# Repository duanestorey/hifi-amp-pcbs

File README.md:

## Hi-Fidelity Amplifier With Active-Crossovers and Room Correction

These are the PCBs representing a two-year passive effort to create, from scratch, an entire hi-fi amplifier with built-in DSP support for active crossovers and room 
correction.  You can [explore the individual PCBs for this project here](/pcbs).

### Overview

The amplifier has the following specifications:

* Four LM3886 68W amplifier channels in two monoblocks
* Five line-level RCA analog inputs
* One phono/vinyl RCA input with built-in amplifier and RIAA correction
* Four 192kHz/24-bit digital SPDIF inputs and one TOSLINK optical
* Multiple 192kHz/24-bit Burr-brown digital to analog converters
* IR remote connection, and built-in web server for configuration and web-app access
* Custom digital signal processor with active-crossovers and room correction ability based on biquad filters and parametric EQ
* Over-the-air code updates and wifi diagnostic information 

### Project Style Guide

#### Power Monitors

There are several INA260 power meters.  

1) MAIN Digital/Analog PSU monitor, address GND/SCL
2) MAIN Positive rail for channel amplifiers, address SCL/GND
3) 7V to 5V converter, address GND/GND
4) 7V to 3V converter, address GND/3V
5) Positive analog converter,  3V/GND
6) Entire 7V converter, 3V/3V

#### Temperature Sensors

1) Microprocessor board, address GND/GND
2) Digital/Analog PSU, address GND/3V#
3) Monoblocks 1, address 3V3/GND and 3V3/3V3
4) DSP, address float/GND

#### LED lights and resistors

The following voltages and LED colours should be used for consistency. In general, all LEDs are set at 2ma of current are 0603 size.

##### Digital Voltages

- 3.3V - Blue, set to ~2ma using 150R 
- 5.0V - Red, set to ~2ma using 1.3K

##### Analog Voltages

* +3.3V - Yellow, set to ~2ma using 620R
* +9.5V - Yellow, set to ~2ma using 3.6K
* -9.5V - Blue, set to ~2ma using 3.3K
* +34V - Yellow, set to ~2ma using 16K
* -34V - Blue, set to ~2ma using 16K
* 12V - Red, set to ~2ma using 4.7K
* Positive DC - Yellow, set to 2ma
* Negative DC - Blue, set to 2ma

#### SPDIF

- TODO: ADded more inputs
- TODO: Maybe add isolation transformers
- TODO: Change ground plane so SPDIF ground doesn't interfere with analog DAC ground

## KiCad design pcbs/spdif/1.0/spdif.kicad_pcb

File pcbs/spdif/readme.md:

## SPDIF transceiver 

This board provides decoding for up to 5 SPDIF/TOSLINK digital audio connections.  It allows has two I2S inputs (one for the microprocessor, and one from the analog ADC board) which can be routed to the output.

### Version History

- 1.0: Initial Release

### Speciality Compenents

* DIX9211 216-kHz Digital Audio Interface Transceiver

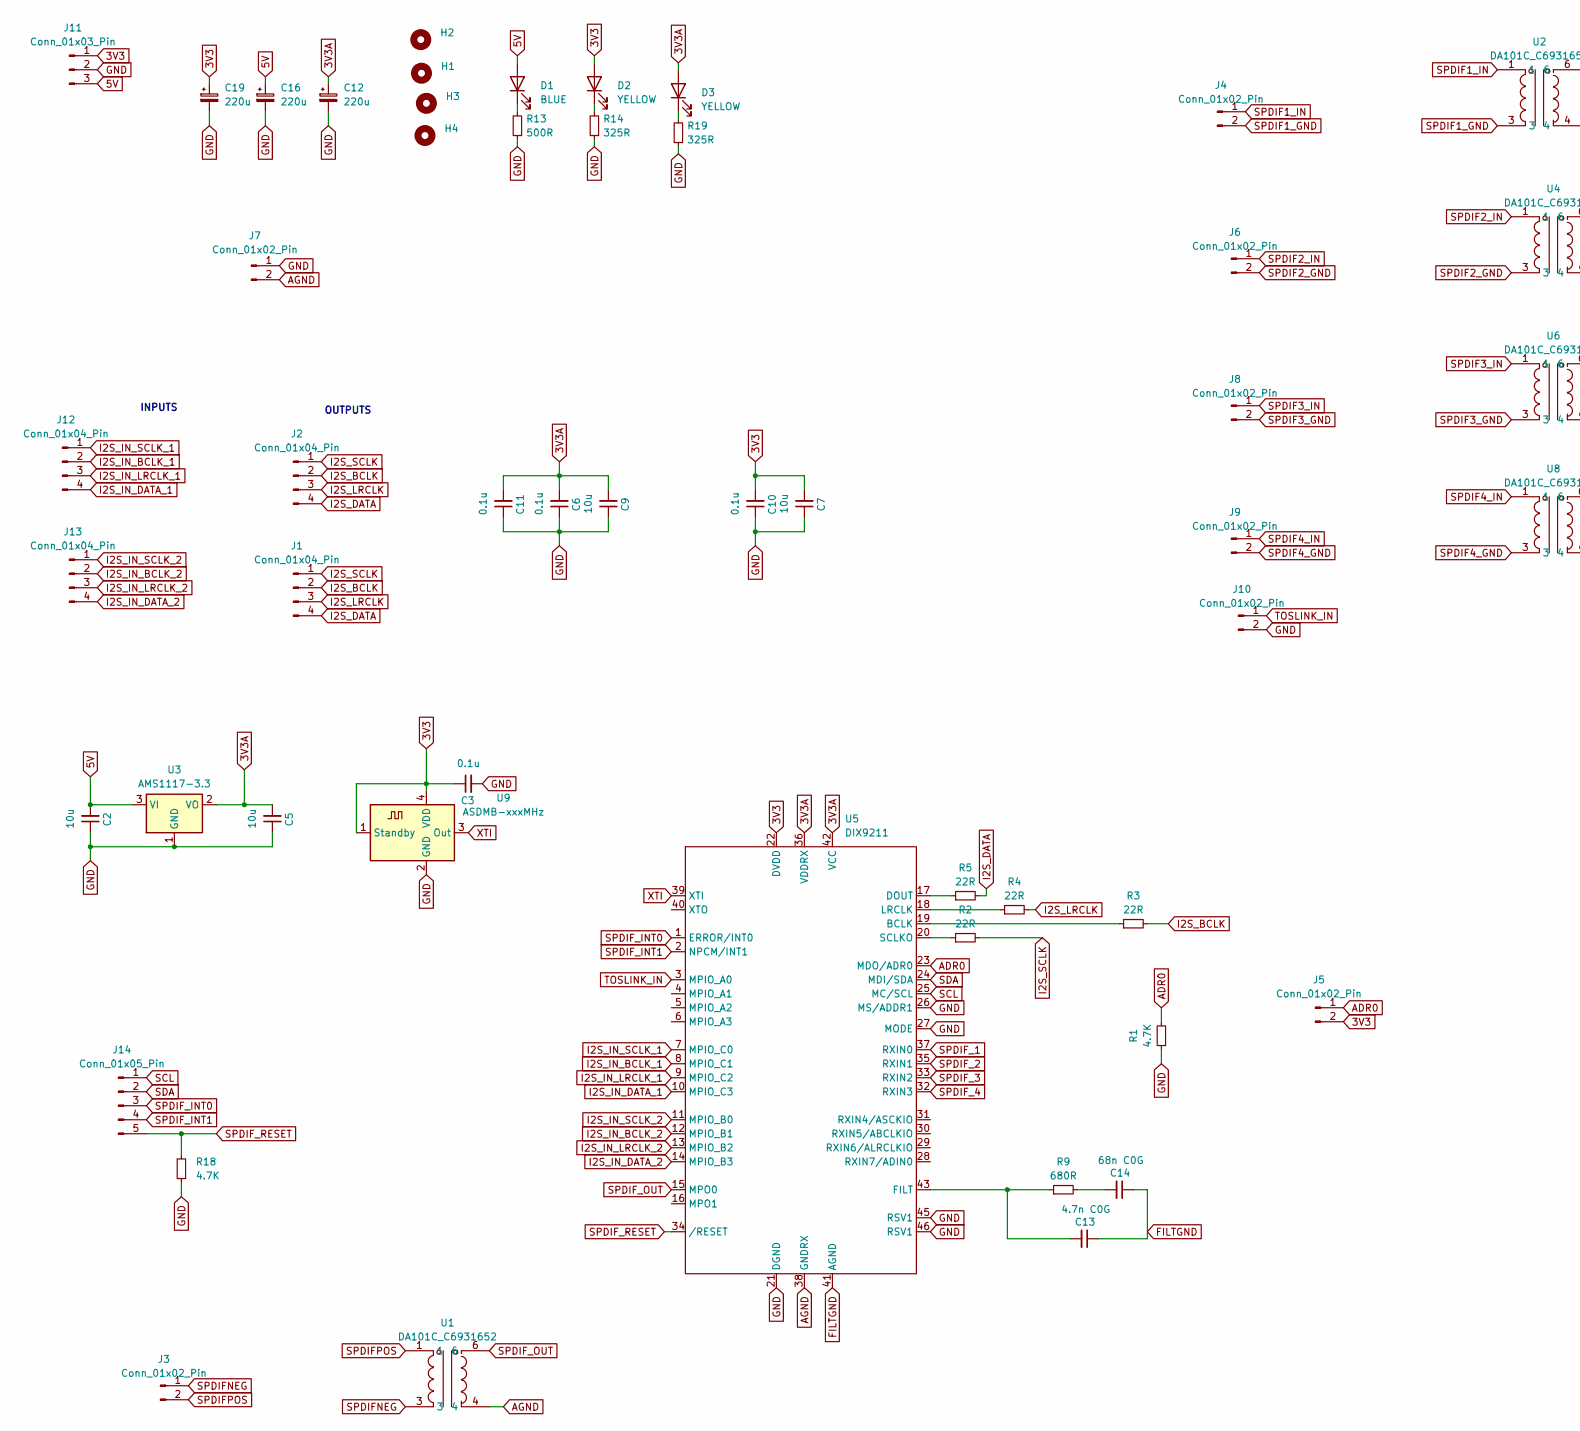
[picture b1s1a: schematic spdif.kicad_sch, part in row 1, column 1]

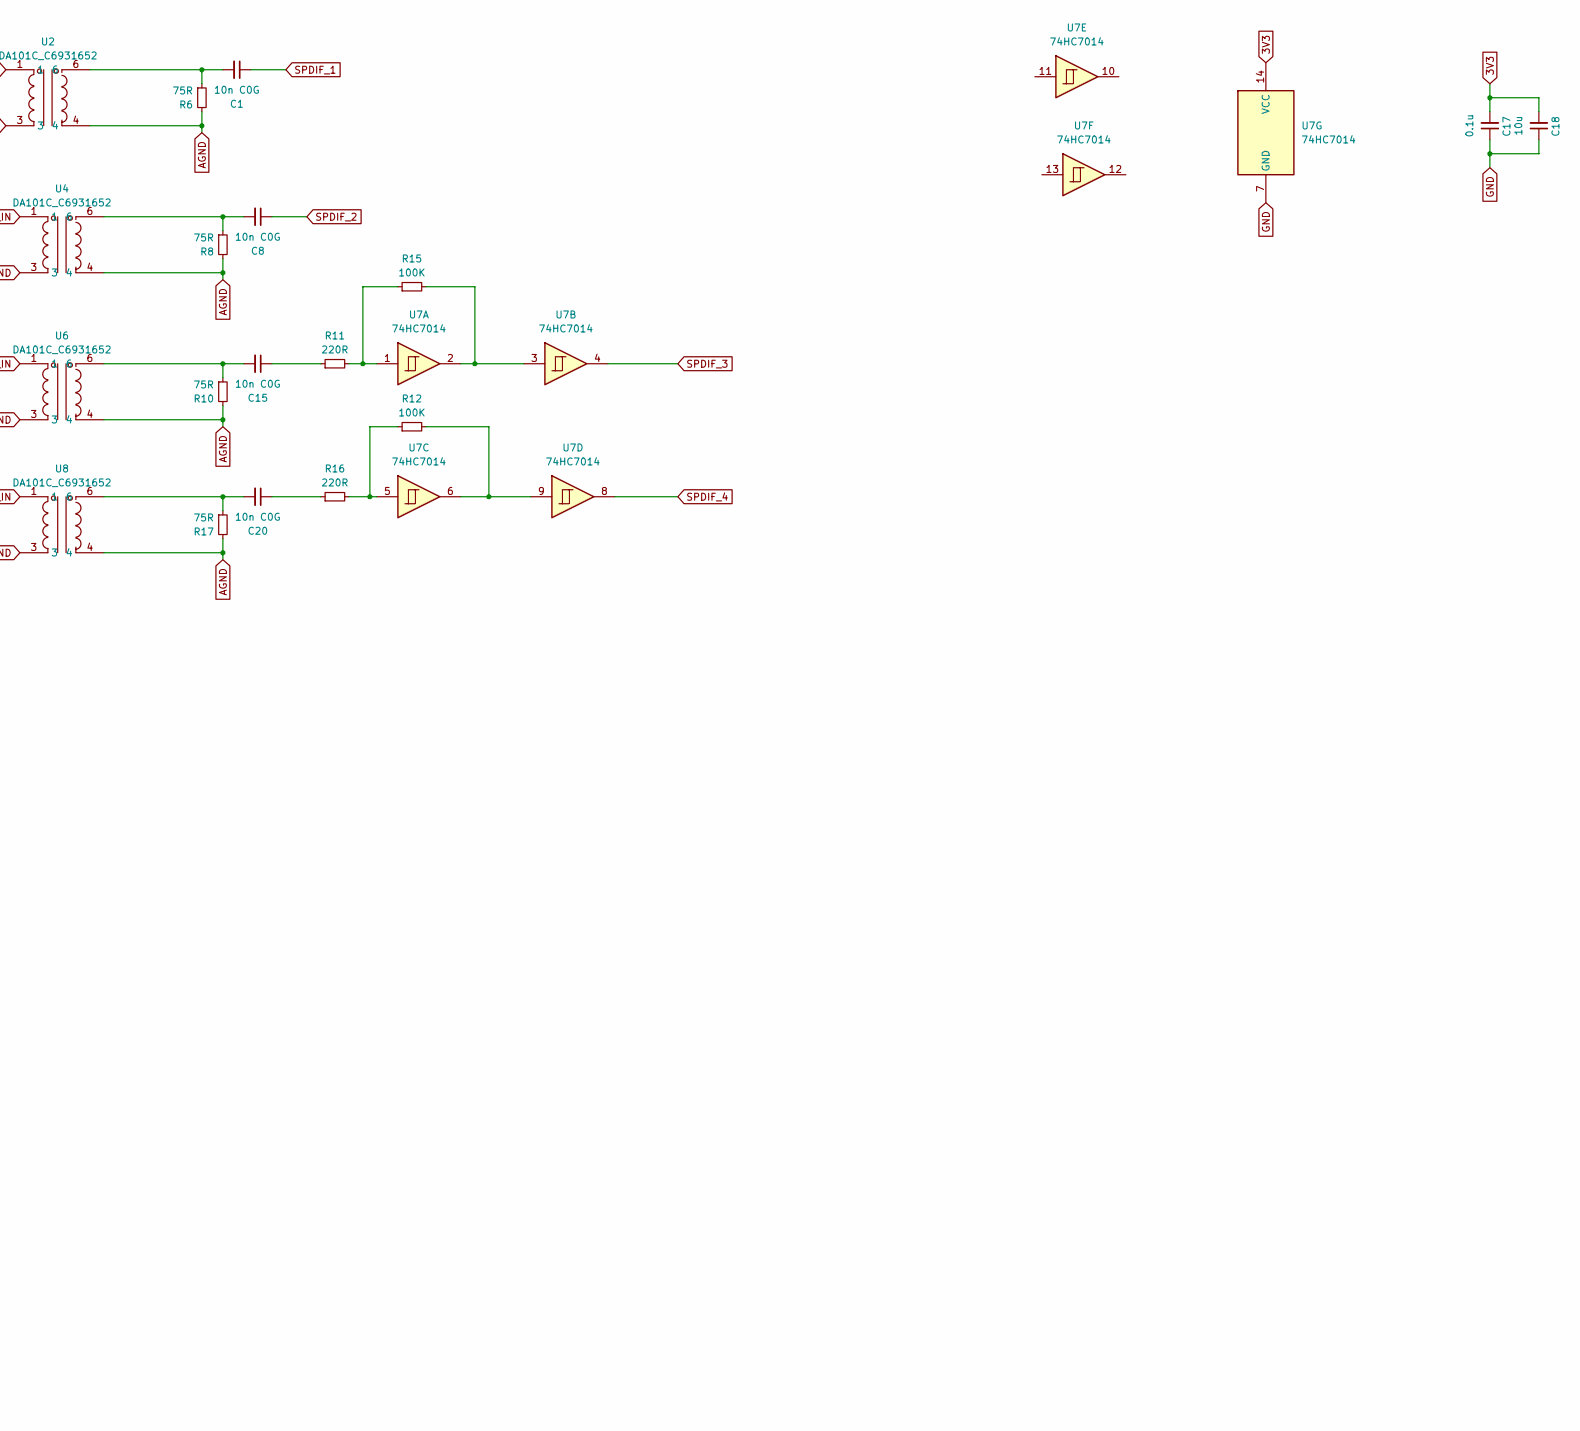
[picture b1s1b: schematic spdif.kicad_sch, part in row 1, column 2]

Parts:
C1, C8, C15, C20: 10n C0G; C_0805_2012Metric_Pad1.18x1.45mm_HandSolder; Mouser 791-0805N103G250CT
C2, C5, C7, C9, C18: 10u; C_1206_3216Metric_Pad1.33x1.80mm_HandSolder
C3, C6, C10, C11, C17: 0.1u; C_0805_2012Metric_Pad1.18x1.45mm_HandSolder
C12, C16, C19: 220u; CP_Radial_D6.3mm_P2.50mm
C13: 4.7n C0G; C_0603_1608Metric; Mouser 791-0603N472F500CT
C14: 68n C0G; C_1206_3216Metric; Mouser 81-GRM3195C1H683JA5D
D1: BLUE; LED_0603_1608Metric
D2, D3: YELLOW; LED_0603_1608Metric
H1, H2, H3, H4: MountingHole; MountingHole_3.2mm_M3_DIN965_Pad_TopOnly
J1: Conn_01x04_Pin; PinHeader_1x04_P2.54mm_Vertical
J2, J12, J13: Conn_01x04_Pin; JST_PH_B4B-PH-K_1x04_P2.00mm_Vertical
J3, J4, J6, J8, J9, J10: Conn_01x02_Pin; JST_XH_B2B-XH-A_1x02_P2.50mm_Vertical
J5, J7: Conn_01x02_Pin; PinHeader_1x02_P2.54mm_Vertical
J11: Conn_01x03_Pin; JST_PH_B3B-PH-K_1x03_P2.00mm_Vertical
J14: Conn_01x05_Pin; JST_PH_B5B-PH-K_1x05_P2.00mm_Vertical
R1, R18: 4.7K; R_0603_1608Metric
R2: 22R; R_0805_2012Metric
R3, R4, R5: 22R; R_0805_2012Metric; Mouser 603-RT0805FRE0722RL
R6, R8, R10, R17: 75R; R_0603_1608Metric_Pad0.98x0.95mm_HandSolder; Mouser 71-CRCW0603-75-E3
R9: 680R; R_0603_1608Metric; Mouser 603-RT0603FRE07680RL
R11, R16: 220R; R_0603_1608Metric_Pad0.98x0.95mm_HandSolder; Mouser 71-CRCW0603-75-E3
R12, R15: 100K; R_0603_1608Metric_Pad0.98x0.95mm_HandSolder; Mouser 71-CRCW0603-75-E3
R13: 500R; R_0603_1608Metric_Pad0.98x0.95mm_HandSolder
R14, R19: 325R; R_0603_1608Metric_Pad0.98x0.95mm_HandSolder
U1, U2, U4, U6, U8: DA101C_C6931652; XFMR-TH_4P-L9.5-W9.0-P5.08-LS10.2_C9900096976; LCSC Part C6931652
U3: AMS1117-3.3; SOT-223-3_TabPin2
U5: DIX9211; LQFP-48_7x7mm_P0.5mm; Mouser 595-DIX9211PTR
U7: 74HC7014; TSSOP-14_4.4x5mm_P0.65mm; Mouser 771-74HC7014D-T
U9: ASDMB-xxxMHz; Oscillator_SMD_Abracon_ASE-4Pin_3.2x2.5mm; Mouser 346-3225Z24.5760C1KX

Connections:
3V3: C3.1, C7.2, C10.2, C17.2, C18.2, C19.1, D2.2 (A), J5.2, J11.1, U5.22 (DVDD), U7.14 (VCC), U9.1 (Standby), U9.4 (VDD)
3V3A: C5.2, C6.2, C9.2, C11.2, C12.1, D3.2 (A), U3.2 (VO), U5.36 (VDDRX), U5.42 (VCC)
5V: C2.2, C16.1, D1.2 (A), J11.3, U3.3 (VI)
ADR0: J5.1, R1.2, U5.23 (MDO/ADR0)
AGND: J7.2, R6.2, R8.2, R10.2, R17.2, U1.4, U2.4, U4.4, U5.38 (GNDRX), U6.4, U8.4
FILTGND: C13.1, C14.1, U5.41 (AGND)
GND: C2.1, C3.2, C5.1, C6.1, C7.1, C9.1, C10.1, C11.1, C12.2, C16.2, C17.1, C18.1, C19.2, J7.1, J10.2, J11.2, R1.1, R13.1, R14.1, R18.1, R19.1, U3.1 (GND), U5.21 (DGND), U5.26 (MS/ADDR1), U5.27 (MODE), U5.45 (RSV1), U5.46 (RSV1), U7.7 (GND), U9.2 (GND)
I2S_BCLK: J1.2, J2.2, R3.2
I2S_DATA: J1.4, J2.4, R5.2
I2S_IN_BCLK_1: J12.2, U5.8 (MPIO_C1)
I2S_IN_BCLK_2: J13.2, U5.12 (MPIO_B1)
I2S_IN_DATA_1: J12.4, U5.10 (MPIO_C3)
I2S_IN_DATA_2: J13.4, U5.14 (MPIO_B3)
I2S_IN_LRCLK_1: J12.3, U5.9 (MPIO_C2)
I2S_IN_LRCLK_2: J13.3, U5.13 (MPIO_B2)
I2S_IN_SCLK_1: J12.1, U5.7 (MPIO_C0)
I2S_IN_SCLK_2: J13.1, U5.11 (MPIO_B0)
I2S_LRCLK: J1.3, J2.3, R4.2
I2S_SCLK: J1.1, J2.1, R2.2
unnamed: C1.2, R6.1, U2.6
unnamed: C8.2, R8.1, U4.6
unnamed: C14.2, R9.2
unnamed: C15.1, R11.1
unnamed: C15.2, R10.1, U6.6
unnamed: C20.1, R16.1
unnamed: C20.2, R17.1, U8.6
unnamed: D1.1 (K), R13.2
unnamed: D2.1 (K), R14.2
unnamed: D3.1 (K), R19.2
unnamed: R11.2, R15.1, U7.1
unnamed: R12.1, R16.2, U7.5
unnamed: R12.2, U7.6, U7.9
unnamed: R15.2, U7.2, U7.3
unnamed: R3.1, U5.19 (BCLK)
unnamed: R5.1, U5.17 (DOUT)
unnamed: C13.2, R9.1, U5.43 (FILT)
unnamed: R4.1, U5.18 (LRCLK)
unnamed: R2.1, U5.20 (SCLKO)
SCL: J14.1, U5.25 (MC/SCL)
SDA: J14.2, U5.24 (MDI/SDA)
SPDIF1_GND: J4.2, U2.3
SPDIF1_IN: J4.1, U2.1
SPDIF2_GND: J6.2, U4.3
SPDIF2_IN: J6.1, U4.1
SPDIF3_GND: J8.2, U6.3
SPDIF3_IN: J8.1, U6.1
SPDIF4_GND: J9.2, U8.3
SPDIF4_IN: J9.1, U8.1
SPDIFNEG: J3.1, U1.3
SPDIFPOS: J3.2, U1.1
SPDIF_1: C1.1, U5.37 (RXIN0)
SPDIF_2: C8.1, U5.35 (RXIN1)
SPDIF_3: U5.33 (RXIN2), U7.4
SPDIF_4: U5.32 (RXIN3), U7.8
SPDIF_INT0: J14.3, U5.1 (ERROR/INT0)
SPDIF_INT1: J14.4, U5.2 (NPCM/INT1)
SPDIF_OUT: U1.6, U5.15 (MPO0)
SPDIF_RESET: J14.5, R18.2, U5.34 (/RESET)
TOSLINK_IN: J10.1, U5.3 (MPIO_A0)
XTI: U5.39 (XTI), U9.3 (Out)

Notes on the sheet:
OUTPUTS
INPUTS

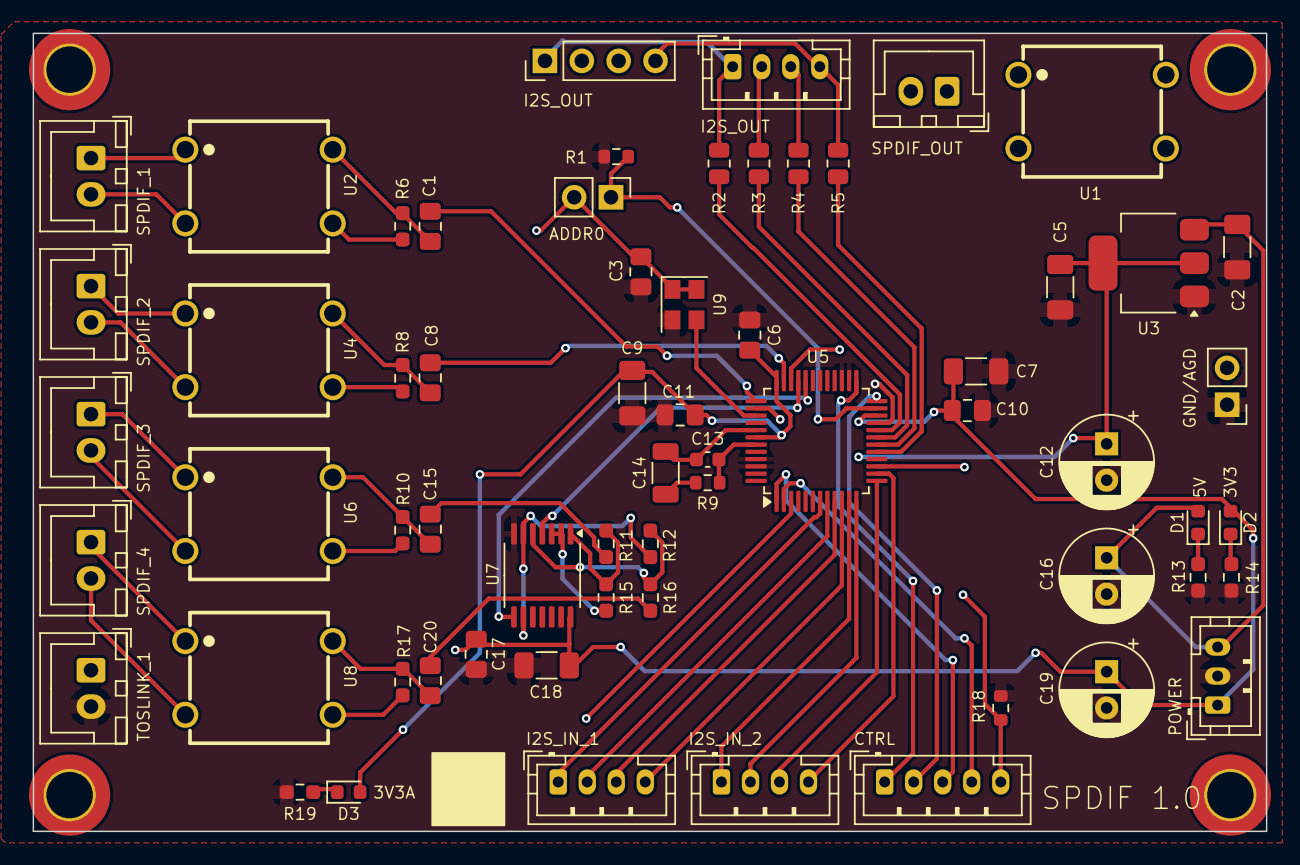
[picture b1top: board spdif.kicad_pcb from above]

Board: 4 copper layers, 85.0 x 55.0 mm, 67 parts (0 on the bottom side), 60 nets.

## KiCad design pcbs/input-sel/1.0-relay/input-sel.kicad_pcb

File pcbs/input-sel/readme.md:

## Line-Input Selector

This PCB allows switching of 4 analog stereo inputs and one 5.1 channel input into 5.1.  Channels that are missing
can be created.  It is based on the AX2358 IC.

### Version History

- 1.0: Initial Release
- 1.2: Did an initial build.  Seems like there is digital noise on the output, likely from the I2C signals sharing the audio ground.  This design now has a digital and analog ground on the board - it'll use the digital ground for the AX2358 IC, but use the analog ground for the channel outputs.

### Speciality Components

* AX2358 Channel switching IC
* Nichicon Muse ES 25V 10uF

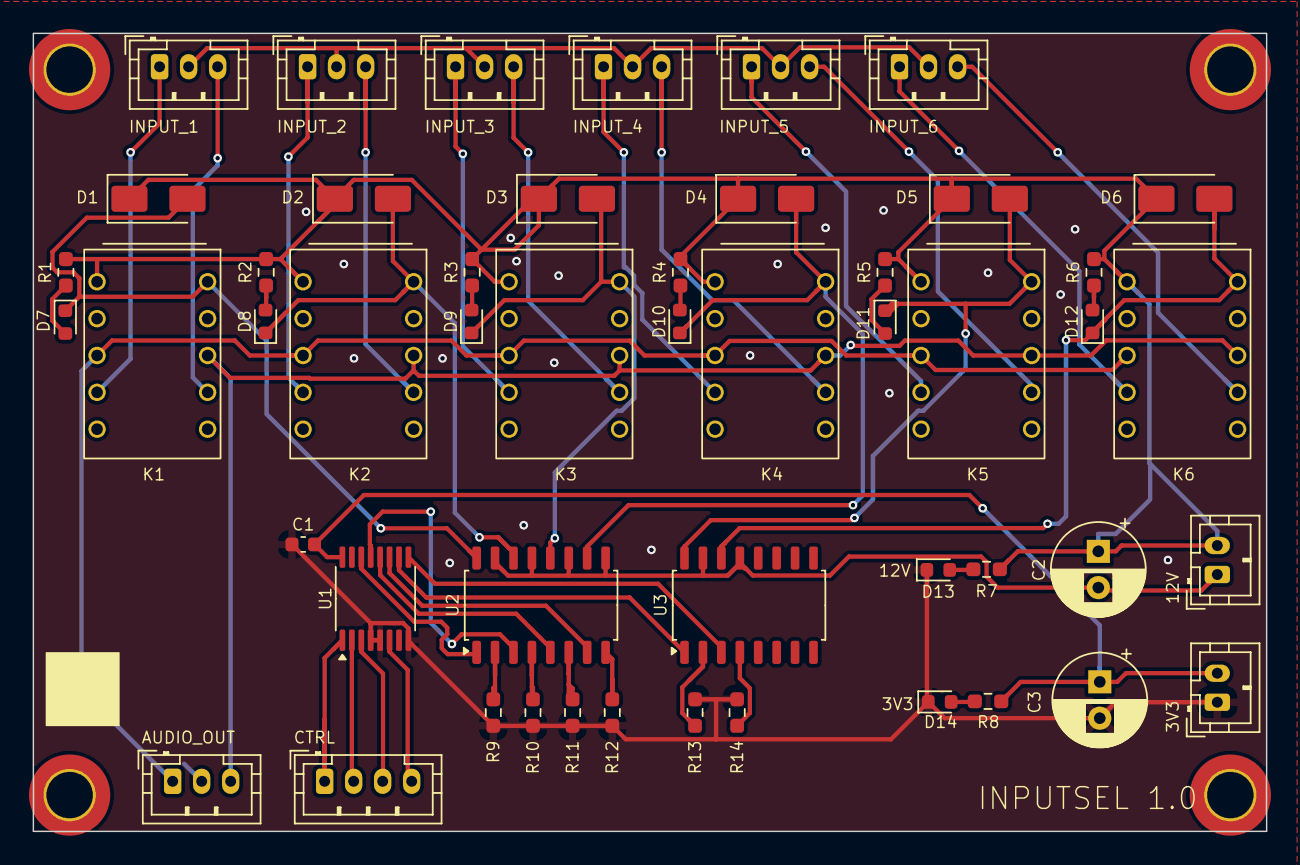
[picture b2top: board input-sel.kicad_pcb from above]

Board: 2 copper layers, 85.0 x 55.0 mm, 54 parts (0 on the bottom side), 49 nets.

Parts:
C1: 0.1u; C_0603_1608Metric
C2, C3: 470u; CP_Radial_D6.3mm_P2.50mm
D1, D2, D3, D4, D5, D6: D; D_SMA
D7, D8, D9, D10, D11, D12, D13: RED; LED_0603_1608Metric
D14: BLUE; LED_0603_1608Metric
H1, H2, H3, H4: MountingHole; MountingHole_3.2mm_M3_DIN965_Pad_TopOnly
J1, J2, J3, J4, J5, J6, J9: Conn_01x03_Pin; JST_PH_B3B-PH-K_1x03_P2.00mm_Vertical
J7, J8: Conn_01x02_Pin; JST_PH_B2B-PH-K_1x02_P2.00mm_Vertical
J10: Conn_01x04_Pin; JST_PH_B4B-PH-K_1x04_P2.00mm_Vertical
K1, K2, K3, K4, K5, K6: EC2-5NU; KEMET EA2
R1, R2, R3, R4, R5, R6: 4.7K; R_0603_1608Metric_Pad0.98x0.95mm_HandSolder
R7: 75R; R_0603_1608Metric_Pad0.98x0.95mm_HandSolder
R8: 150R; R_0603_1608Metric_Pad0.98x0.95mm_HandSolder
R9, R10, R11, R12, R13, R14: 820R; R_0603_1608Metric_Pad0.98x0.95mm_HandSolder
U1: CD74AC238; TSSOP-16_4.4x5mm_P0.65mm
U2, U3: TCMT4600; SOP-16_4.55x10.3mm_P1.27mm

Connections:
3V3: C1.1, C3.1, J8.2, R8.2, U1.16 (VCC)
12V: C2.1, D1.1 (K), D2.1 (K), D3.1 (K), D4.1 (K), D5.1 (K), D6.1 (K), J7.2, K1.1, K2.1, K3.1, K4.1, K5.1, K6.1, R1.2, R2.2, R3.2, R4.2, R5.2, R6.2, R7.2
AGND: J1.2, J2.2, J3.2, J4.2, J5.2, J6.2, J9.2
CTRL1: J10.1, U1.1 (A0)
CTRL2: J10.2, U1.2 (A1)
CTRL3: J10.3, U1.3 (A2)
EN: J10.4, U1.6 (E3)
GND: C1.2, C3.2, D13.1 (K), D14.1 (K), J8.1, R9.2, R10.2, R11.2, R12.2, R13.2, R14.2, U1.4 (~E1), U1.5 (~E2), U1.8 (GND)
unnamed: D1.2 (A), D7.1 (K), K1.12, U2.16
unnamed: D2.2 (A), D8.1 (K), K2.12, U2.14
unnamed: D3.2 (A), D9.1 (K), K3.12, U2.12
unnamed: D7.2 (A), R1.1
unnamed: D8.2 (A), R2.1
unnamed: D9.2 (A), R3.1
unnamed: D10.2 (A), R4.1
unnamed: D4.2 (A), D10.1 (K), K4.12, U2.10
unnamed: D11.2 (A), R5.1
unnamed: D5.2 (A), D11.1 (K), K5.12, U3.16
unnamed: D12.2 (A), R6.1
unnamed: D6.2 (A), D12.1 (K), K6.12, U3.14
unnamed: D13.2 (A), R7.1
unnamed: D14.2 (A), R8.1
unnamed: R9.1, U2.2
unnamed: R10.1, U2.4
unnamed: R11.1, U2.6
unnamed: R12.1, U2.8
unnamed: R13.1, U3.2
unnamed: R14.1, U3.4
OUT_L: J9.1, K1.4, K2.4, K3.4, K4.4, K5.4, K6.4
OUT_R: J9.3, K1.9, K2.9, K3.9, K4.9, K5.9, K6.9
RCA1_L: J1.1, K1.5
RCA1_R: J1.3, K1.8
RCA2_L: J2.1, K2.5
RCA2_R: J2.3, K2.8
RCA3_L: J3.1, K3.5
RCA3_R: J3.3, K3.8
RCA4_L: J4.1, K4.5
RCA4_R: J4.3, K4.8
RCA5_L: J5.1, K5.5
RCA5_R: J5.3, K5.8
RCA6_L: J6.1, K6.5
RCA6_R: J6.3, K6.8
RELAY1: U1.14 (Y1), U2.1
RELAY2: U1.13 (Y2), U2.3
RELAY3: U1.12 (Y3), U2.5
RELAY4: U1.11 (Y4), U2.7
RELAY5: U1.10 (Y5), U3.1
RELAY6: U1.9 (Y6), U3.3
RELAY_GND: C2.2, J7.1, U2.9, U2.11, U2.13, U2.15, U3.13, U3.15

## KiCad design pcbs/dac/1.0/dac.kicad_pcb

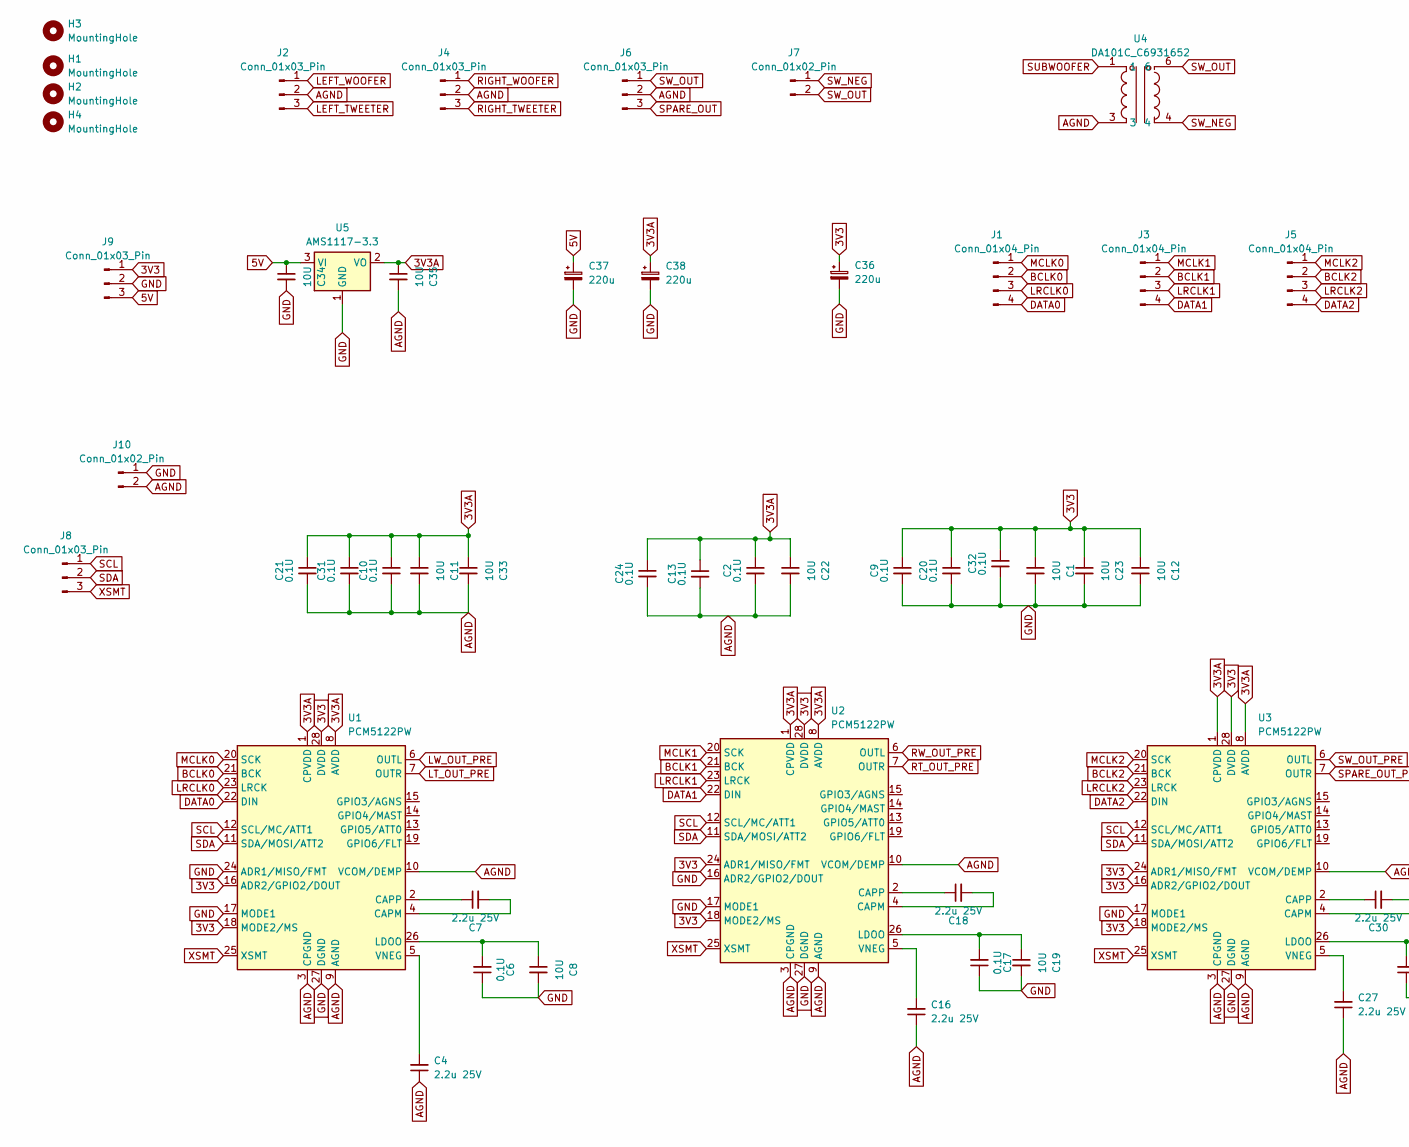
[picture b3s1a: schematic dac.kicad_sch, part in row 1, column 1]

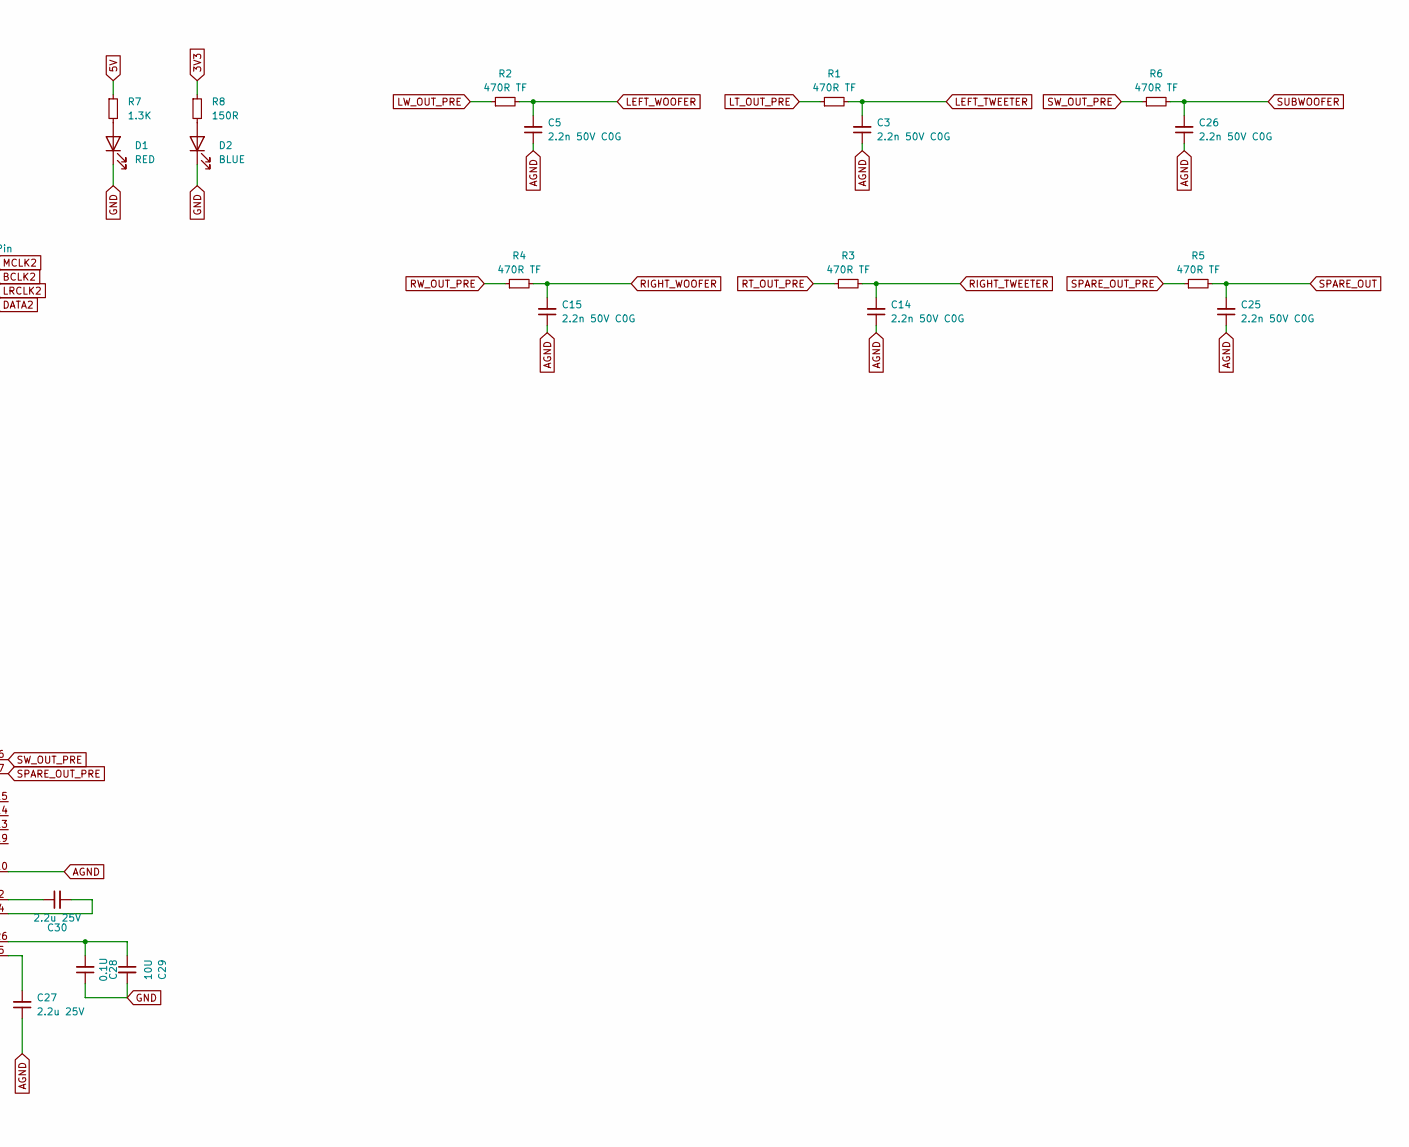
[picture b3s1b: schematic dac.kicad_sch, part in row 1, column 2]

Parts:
C1, C8, C11, C12, C19, C22, C23, C29, C33, C34, C35: 10U; C_1206_3216Metric_Pad1.33x1.80mm_HandSolder
C2, C6, C9, C10, C13, C17, C20, C21, C24, C28, C31, C32: 0.1U; C_0805_2012Metric_Pad1.18x1.45mm_HandSolder
C3, C5, C14, C15: 2.2n 50V C0G; C_0805_2012Metric_Pad1.18x1.45mm_HandSolder; Mouser 791-0805N222F500CT
C4, C16, C27: 2.2u 25V; C_1206_3216Metric_Pad1.33x1.80mm_HandSolder
C7, C18, C30: 2.2u 25V; C_0805_2012Metric_Pad1.18x1.45mm_HandSolder
C25, C26: 2.2n 50V C0G; C_0805_2012Metric_Pad1.18x1.45mm_HandSolder
C36, C37, C38: 220u; CP_Radial_D6.3mm_P2.50mm
D1: RED; LED_0603_1608Metric
D2: BLUE; LED_0603_1608Metric
H1, H2, H3, H4: MountingHole; MountingHole_3.2mm_M3_DIN965_Pad_TopOnly
J1, J3, J5: Conn_01x04_Pin; JST_PH_B4B-PH-K_1x04_P2.00mm_Vertical
J2, J4, J6, J8, J9: Conn_01x03_Pin; JST_PH_B3B-PH-K_1x03_P2.00mm_Vertical
J7: Conn_01x02_Pin; JST_PH_B2B-PH-K_1x02_P2.00mm_Vertical
J10: Conn_01x02_Pin; PinHeader_1x02_P2.54mm_Vertical
R1, R2, R3, R4, R5, R6: 470R TF; R_0805_2012Metric_Pad1.20x1.40mm_HandSolder; Mouser 603-RT0805FRE07470RL
R7: 1.3K; R_0603_1608Metric_Pad0.98x0.95mm_HandSolder
R8: 150R; R_0603_1608Metric_Pad0.98x0.95mm_HandSolder
U1, U2, U3: PCM5122PW; TSSOP-28_4.4x9.7mm_P0.65mm; Mouser 595-PCM5142PWR
U4: DA101C_C6931652; XFMR-TH_4P-L9.5-W9.0-P5.08-LS10.2_C9900096976; LCSC Part C6931652
U5: AMS1117-3.3; SOT-223-3_TabPin2

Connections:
3V3: C1.1, C9.1, C12.1, C20.1, C23.1, C32.1, C36.1, J9.1, R8.1, U1.16 (ADR2/GPIO2/DOUT), U1.18 (MODE2/MS), U1.28 (DVDD), U2.18 (MODE2/MS), U2.24 (ADR1/MISO/FMT), U2.28 (DVDD), U3.16 (ADR2/GPIO2/DOUT), U3.18 (MODE2/MS), U3.24 (ADR1/MISO/FMT), U3.28 (DVDD)
3V3A: C2.1, C10.1, C11.1, C13.1, C21.1, C22.1, C24.1, C31.1, C33.1, C35.1, C38.1, U1.1 (CPVDD), U1.8 (AVDD), U2.1 (CPVDD), U2.8 (AVDD), U3.1 (CPVDD), U3.8 (AVDD), U5.2 (VO)
5V: C34.1, C37.1, J9.3, R7.1, U5.3 (VI)
AGND: C2.2, C3.1, C4.1, C5.1, C10.2, C11.2, C13.2, C14.1, C15.1, C16.1, C21.2, C22.2, C24.2, C25.1, C26.1, C27.1, C31.2, C33.2, C35.2, J2.2, J4.2, J6.2, J10.2, U1.3 (CPGND), U1.9 (AGND), U1.10 (VCOM/DEMP), U2.3 (CPGND), U2.9 (AGND), U2.10 (VCOM/DEMP), U3.3 (CPGND), U3.9 (AGND), U3.10 (VCOM/DEMP), U4.3; also elsewhere on the board
BCLK0: J1.2, U1.21 (BCK)
BCLK1: J3.2, U2.21 (BCK)
BCLK2: J5.2, U3.21 (BCK)
DATA0: J1.4, U1.22 (DIN)
DATA1: J3.4, U2.22 (DIN)
DATA2: J5.4, U3.22 (DIN)
GND: C1.2, C6.1, C8.2, C9.2, C12.2, C17.1, C19.2, C20.2, C23.2, C28.1, C29.2, C32.2, C34.2, C36.2, C37.2, C38.2, D1.1 (K), D2.1 (K), J9.2, J10.1, U1.17 (MODE1), U1.24 (ADR1/MISO/FMT), U1.27 (DGND), U2.16 (ADR2/GPIO2/DOUT), U2.17 (MODE1), U2.27 (DGND), U3.17 (MODE1), U3.27 (DGND), U5.1 (GND)
LEFT_TWEETER: C3.2, J2.3, R1.2
LEFT_WOOFER: C5.2, J2.1, R2.2
LRCLK0: J1.3, U1.23 (LRCK)
LRCLK1: J3.3, U2.23 (LRCK)
LRCLK2: J5.3, U3.23 (LRCK)
LT_OUT_PRE: R1.1, U1.7 (OUTR)
LW_OUT_PRE: R2.1, U1.6 (OUTL)
MCLK0: J1.1, U1.20 (SCK)
MCLK1: J3.1, U2.20 (SCK)
MCLK2: J5.1, U3.20 (SCK)
unnamed: D1.2 (A), R7.2
unnamed: D2.2 (A), R8.2
unnamed: C7.2, U1.4 (CAPM)
unnamed: C7.1, U1.2 (CAPP)
unnamed: C6.2, C8.1, U1.26 (LDOO)
unnamed: C4.2, U1.5 (VNEG)
unnamed: C18.2, U2.4 (CAPM)
unnamed: C18.1, U2.2 (CAPP)
unnamed: C17.2, C19.1, U2.26 (LDOO)
unnamed: C16.2, U2.5 (VNEG)
unnamed: C30.2, U3.4 (CAPM)
unnamed: C30.1, U3.2 (CAPP)
unnamed: C28.2, C29.1, U3.26 (LDOO)
unnamed: C27.2, U3.5 (VNEG)
RIGHT_TWEETER: C14.2, J4.3, R3.2
RIGHT_WOOFER: C15.2, J4.1, R4.2
RT_OUT_PRE: R3.1, U2.7 (OUTR)
RW_OUT_PRE: R4.1, U2.6 (OUTL)
SCL: J8.1, U1.12 (SCL/MC/ATT1), U2.12 (SCL/MC/ATT1), U3.12 (SCL/MC/ATT1)
SDA: J8.2, U1.11 (SDA/MOSI/ATT2), U2.11 (SDA/MOSI/ATT2), U3.11 (SDA/MOSI/ATT2)
SPARE_OUT: C25.2, J6.3, R5.2
SPARE_OUT_PRE: R5.1, U3.7 (OUTR)
SUBWOOFER: C26.2, R6.2, U4.1; also elsewhere on the board
SW_NEG: J7.1, U4.4; also elsewhere on the board
SW_OUT: J6.1, J7.2, U4.6; also elsewhere on the board
SW_OUT_PRE: R6.1, U3.6 (OUTL)
XSMT: J8.3, U1.25 (XSMT), U2.25 (XSMT), U3.25 (XSMT)

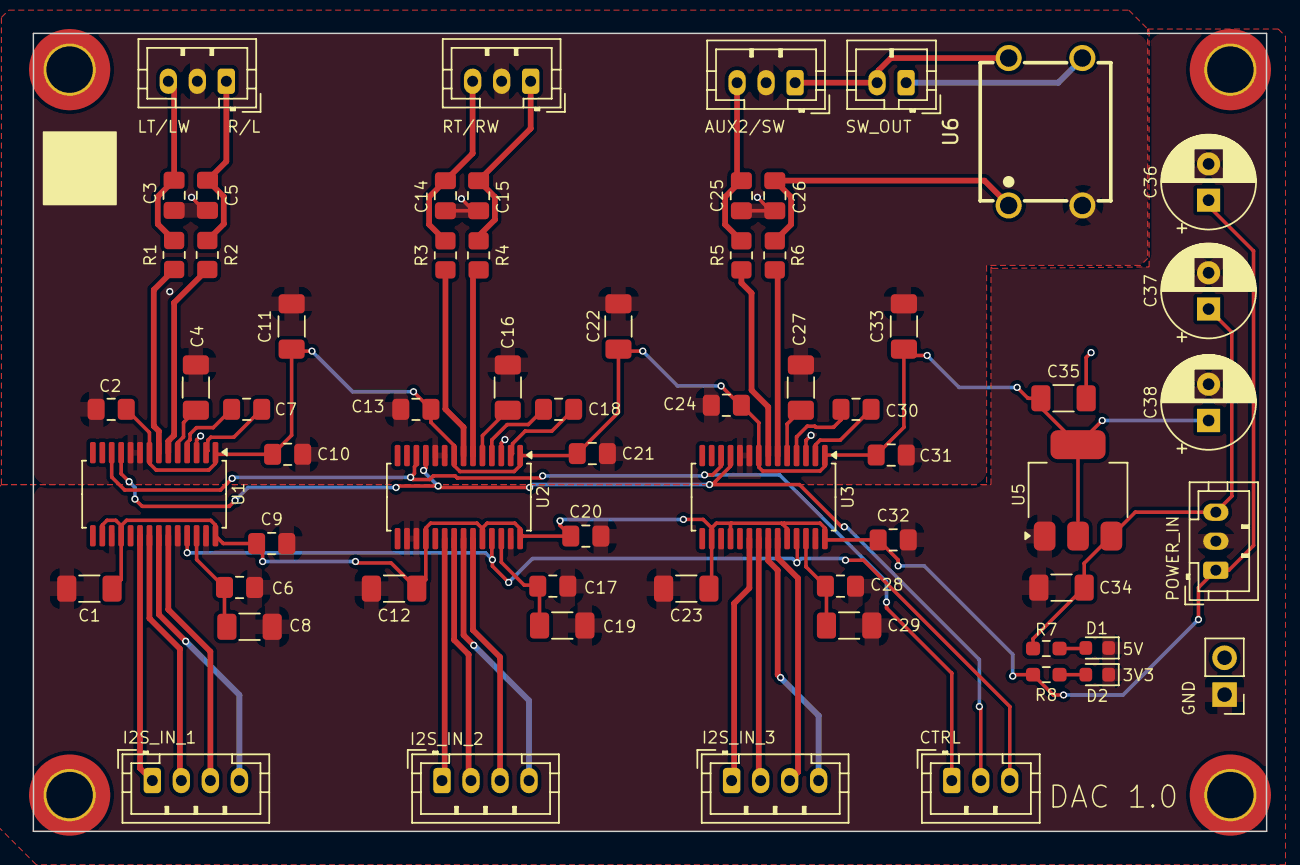
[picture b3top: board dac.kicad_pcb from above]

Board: 2 copper layers, 85.0 x 55.0 mm, 67 parts (0 on the bottom side), 48 nets.

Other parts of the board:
U6: DA101C_C6931652; XFMR-TH_4P-L9.5-W9.0-P5.08-LS10.2_C9900096976

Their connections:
AGND: U6.3; also elsewhere on the board
SUBWOOFER: U6.1; also elsewhere on the board
SW_NEG: U6.4; also elsewhere on the board
SW_OUT: U6.6; also elsewhere on the board
